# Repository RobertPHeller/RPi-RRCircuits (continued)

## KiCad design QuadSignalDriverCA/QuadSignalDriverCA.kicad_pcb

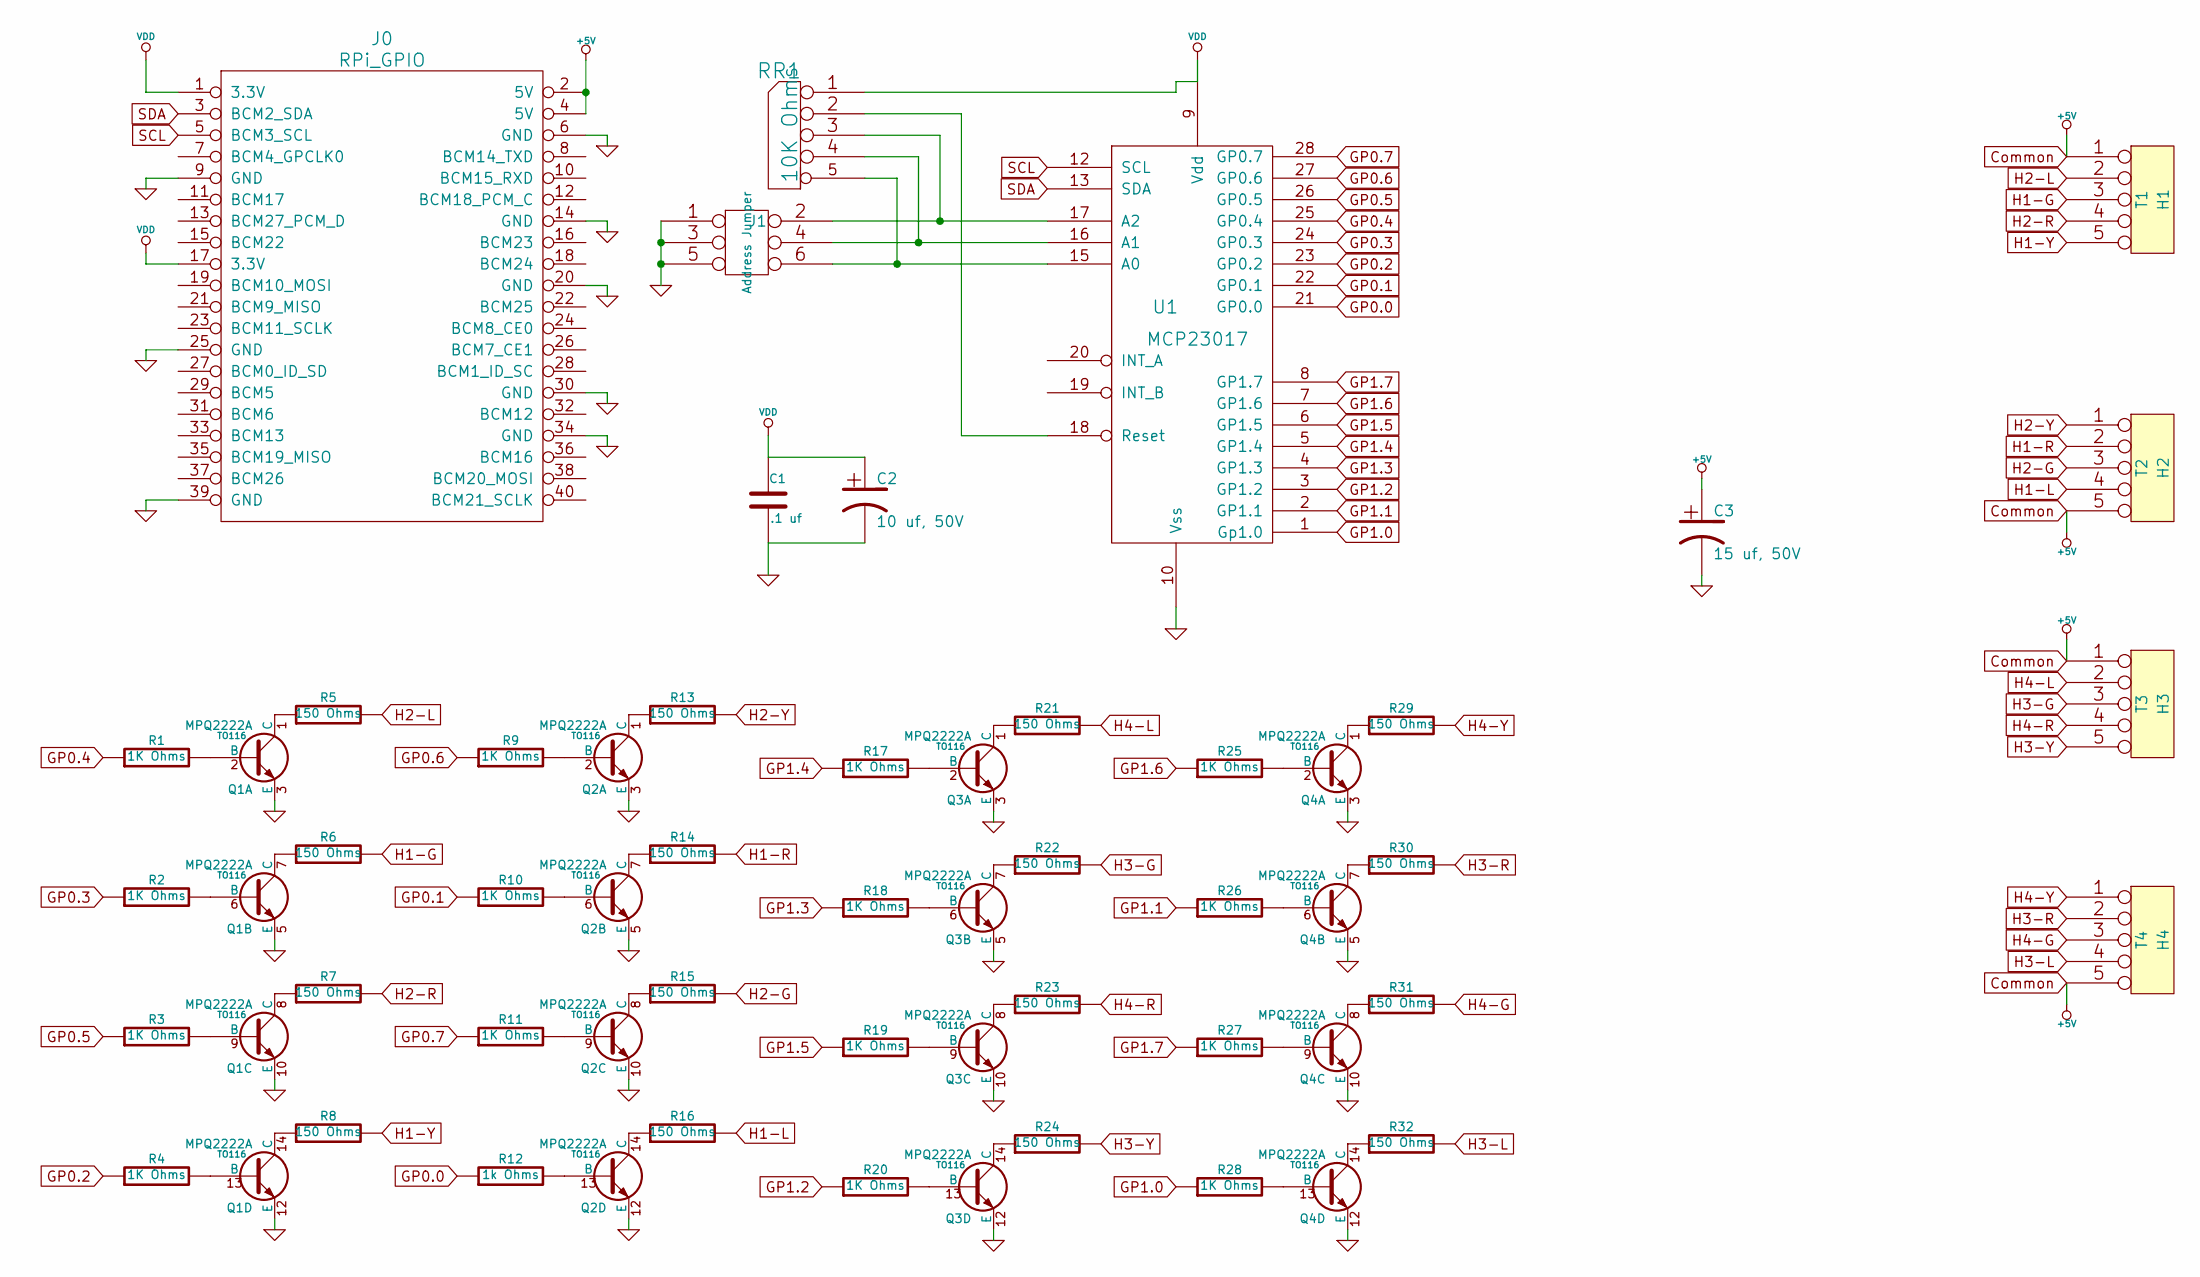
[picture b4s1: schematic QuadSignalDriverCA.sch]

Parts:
C1: .1 uf
C2: 10 uf, 50V
C3: 15 uf, 50V
J0: RPi_GPIO; Pin_Header_Straight_2x20
J1: Address Jumper
Q1, Q2, Q3, Q4: MPQ2222A; TO116
R1, R2, R3, R4, R9, R10, R11, R17, R18, R19, R20, R25, R26, R27, R28: 1K Ohms
R5, R6, R7, R8, R13, R14, R15, R16, R21, R22, R23, R24, R29, R30, R31, R32: 150 Ohms
R12: 1k Ohms
RR1: 10K Ohms
T1: H1
T2: H2
T3: H3
T4: H4
U1: MCP23017

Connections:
Common: C3.1, J0.2 (5V), J0.4 (5V), T1.1, T2.5, T3.1, T4.5
GND: C1.2, C2.2, C3.2, J0.6 (GND), J0.9 (GND), J0.14 (GND), J0.20 (GND), J0.25 (GND), J0.30 (GND), J0.34 (GND), J0.39 (GND), J1.1, J1.3, J1.5, Q1.3 (E), Q1.5 (E), Q1.10 (E), Q1.12 (E), Q2.3 (E), Q2.5 (E), Q2.10 (E), Q2.12 (E), Q3.3 (E), Q3.5 (E), Q3.10 (E), Q3.12 (E), Q4.3 (E), Q4.5 (E), Q4.10 (E), Q4.12 (E), U1.10 (Vss)
GP0.0: R12.1, U1.21 (GP0.0)
GP0.1: R10.1, U1.22 (GP0.1)
GP0.2: R4.1, U1.23 (GP0.2)
GP0.3: R2.1, U1.24 (GP0.3)
GP0.4: R1.1, U1.25 (GP0.4)
GP0.5: R3.1, U1.26 (GP0.5)
GP0.6: R9.1, U1.27 (GP0.6)
GP0.7: R11.1, U1.28 (GP0.7)
GP1.0: R28.1, U1.1 (Gp1.0)
GP1.1: R26.1, U1.2 (GP1.1)
GP1.2: R20.1, U1.3 (GP1.2)
GP1.3: R18.1, U1.4 (GP1.3)
GP1.4: R17.1, U1.5 (GP1.4)
GP1.5: R19.1, U1.6 (GP1.5)
GP1.6: R25.1, U1.7 (GP1.6)
GP1.7: R27.1, U1.8 (GP1.7)
H1-G: R6.2, T1.3
H1-L: R16.2, T2.4
H1-R: R14.2, T2.2
H1-Y: R8.2, T1.5
H2-G: R15.2, T2.3
H2-L: R5.2, T1.2
H2-R: R7.2, T1.4
H2-Y: R13.2, T2.1
H3-G: R22.2, T3.3
H3-L: R32.2, T4.4
H3-R: R30.2, T4.2
H3-Y: R24.2, T3.5
H4-G: R31.2, T4.3
H4-L: R21.2, T3.2
H4-R: R23.2, T3.4
H4-Y: R29.2, T4.1
unnamed: Q4.14 (C), R32.1
unnamed: Q4.13 (B), R28.2
unnamed: J1.6, RR1.5, U1.15 (A0)
unnamed: J1.4, RR1.4, U1.16 (A1)
unnamed: J1.2, RR1.3, U1.17 (A2)
unnamed: RR1.2, U1.18 (Reset)
unnamed: Q1.6 (B), R2.2
unnamed: Q1.7 (C), R6.1
unnamed: Q1.1 (C), R5.1
unnamed: Q1.2 (B), R1.2
unnamed: Q2.2 (B), R9.2
unnamed: Q2.1 (C), R13.1
unnamed: Q1.14 (C), R8.1
unnamed: Q1.13 (B), R4.2
unnamed: Q1.8 (C), R7.1
unnamed: Q1.9 (B), R3.2
unnamed: Q4.2 (B), R25.2
unnamed: Q4.1 (C), R29.1
unnamed: Q3.14 (C), R24.1
unnamed: Q3.13 (B), R20.2
unnamed: Q3.8 (C), R23.1
unnamed: Q3.9 (B), R19.2
unnamed: Q4.8 (C), R31.1
unnamed: Q4.9 (B), R27.2
unnamed: Q4.7 (C), R30.1
unnamed: Q4.6 (B), R26.2
unnamed: Q2.8 (C), R15.1
unnamed: Q2.9 (B), R11.2
unnamed: Q2.7 (C), R14.1
unnamed: Q2.6 (B), R10.2
unnamed: Q3.7 (C), R22.1
unnamed: Q3.6 (B), R18.2
unnamed: Q3.1 (C), R21.1
unnamed: Q3.2 (B), R17.2
unnamed: Q2.14 (C), R16.1
unnamed: Q2.13 (B), R12.2
SCL: J0.5 (BCM3_SCL), U1.12 (SCL)
SDA: J0.3 (BCM2_SDA), U1.13 (SDA)
VDD: C1.1, C2.1, J0.1 (3.3V), J0.17 (3.3V), RR1.1 (COM), U1.9 (Vdd)

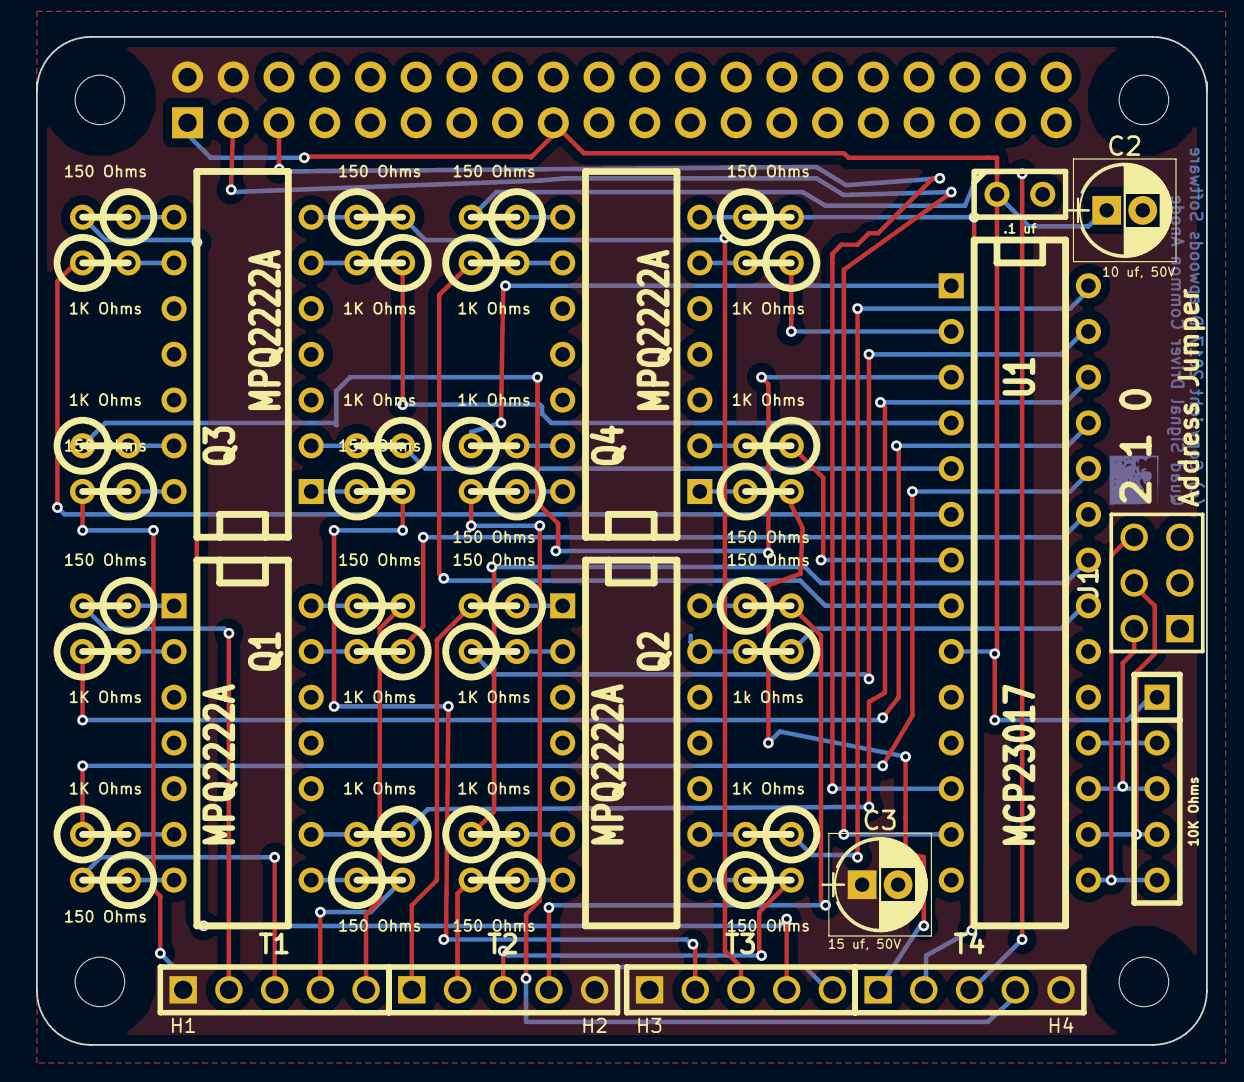
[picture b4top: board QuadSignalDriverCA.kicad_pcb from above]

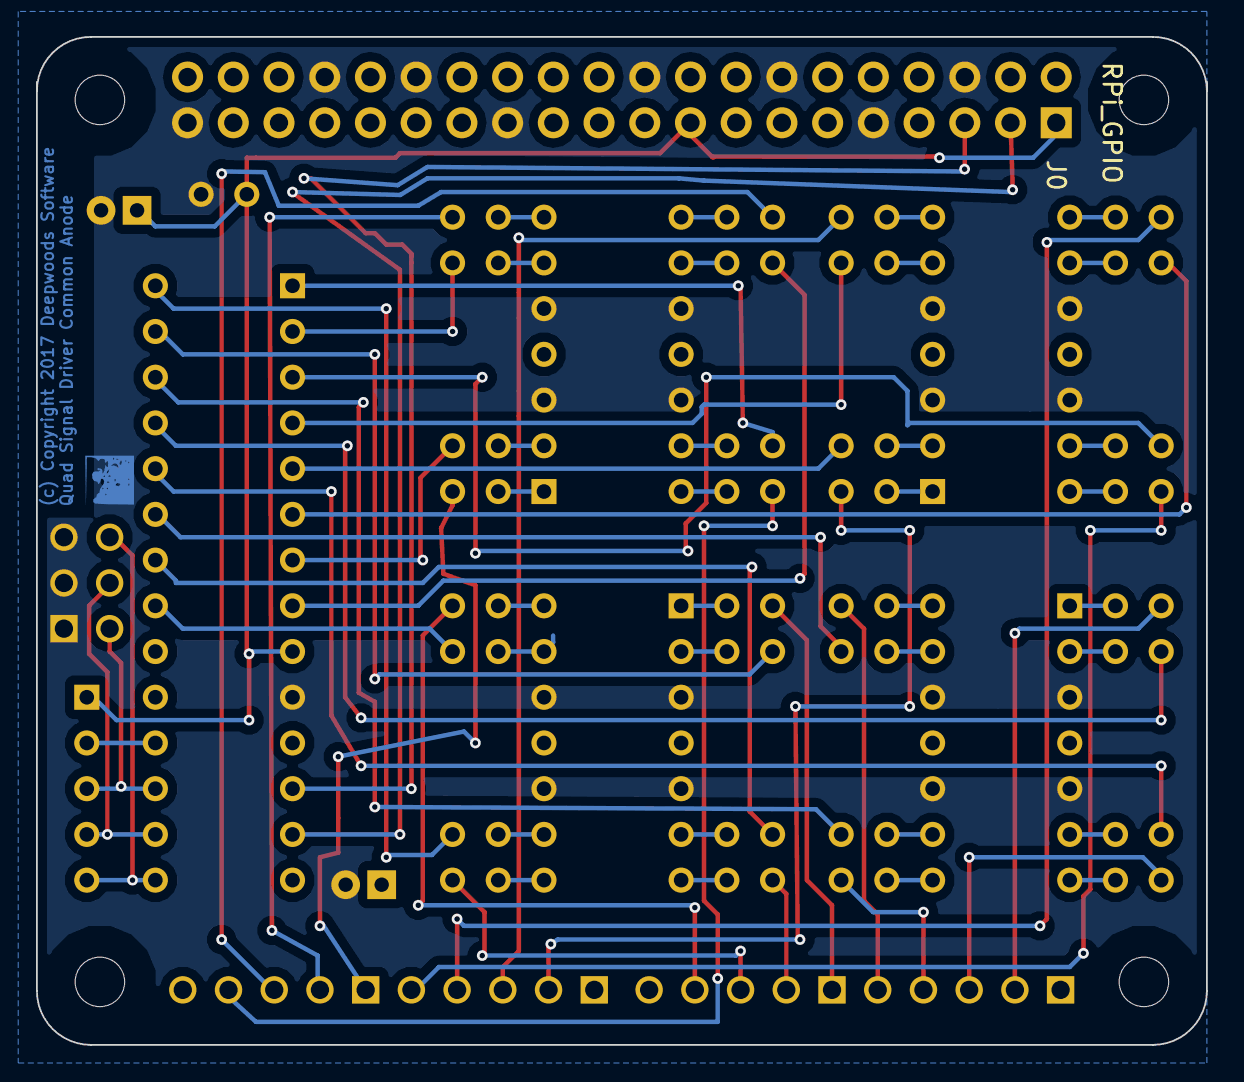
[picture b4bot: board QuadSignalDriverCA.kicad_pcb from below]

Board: 2 copper layers, 65.0 x 56.0 mm, 51 parts (5 on the bottom side), 73 nets.

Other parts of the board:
H1, H2, H3, H4: RPi_Hat_Mounting_Hole

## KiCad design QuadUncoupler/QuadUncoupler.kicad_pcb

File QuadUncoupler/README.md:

# QuadUncoupler

This is a generic qad version of DualUncouplerHAT.

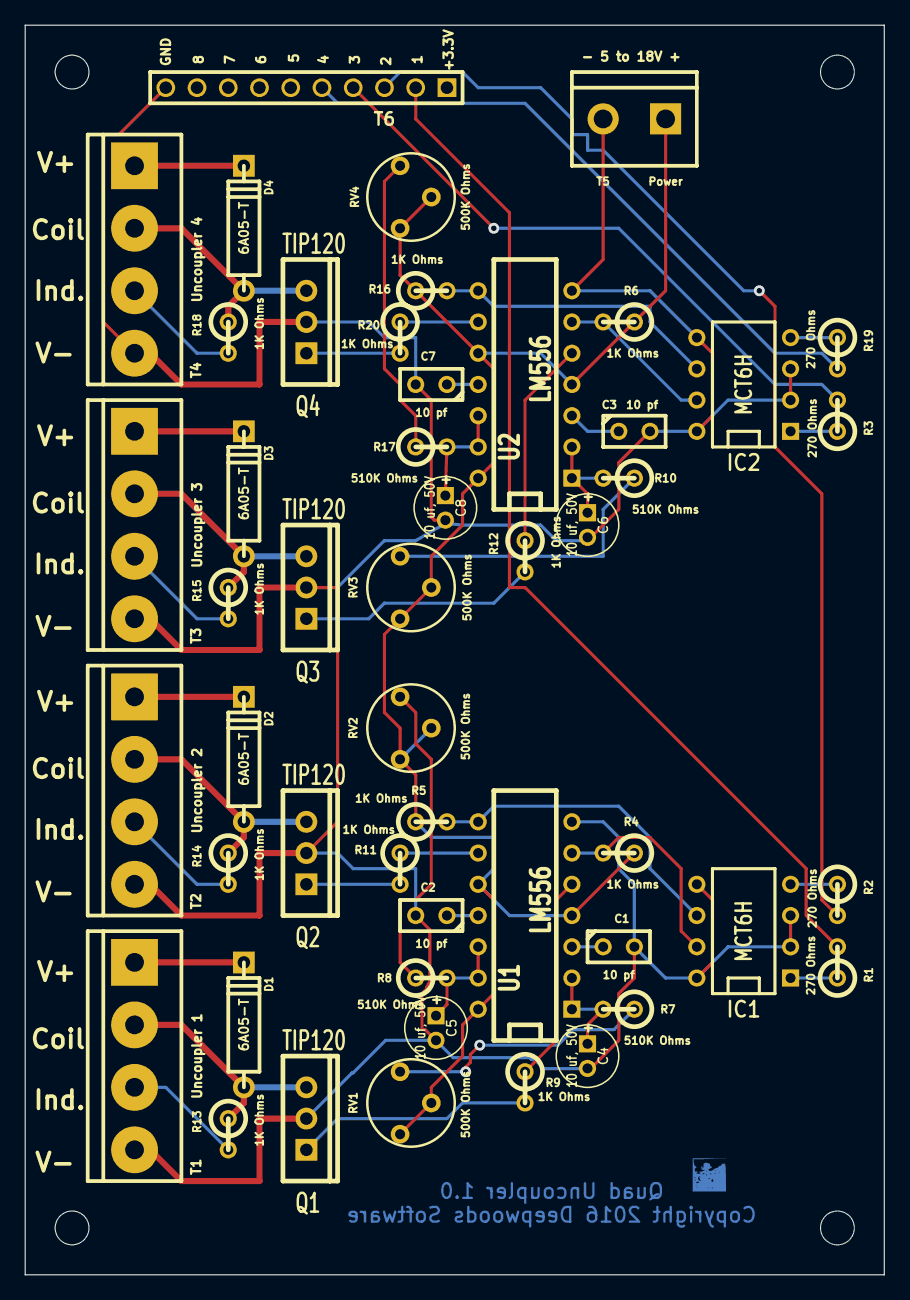
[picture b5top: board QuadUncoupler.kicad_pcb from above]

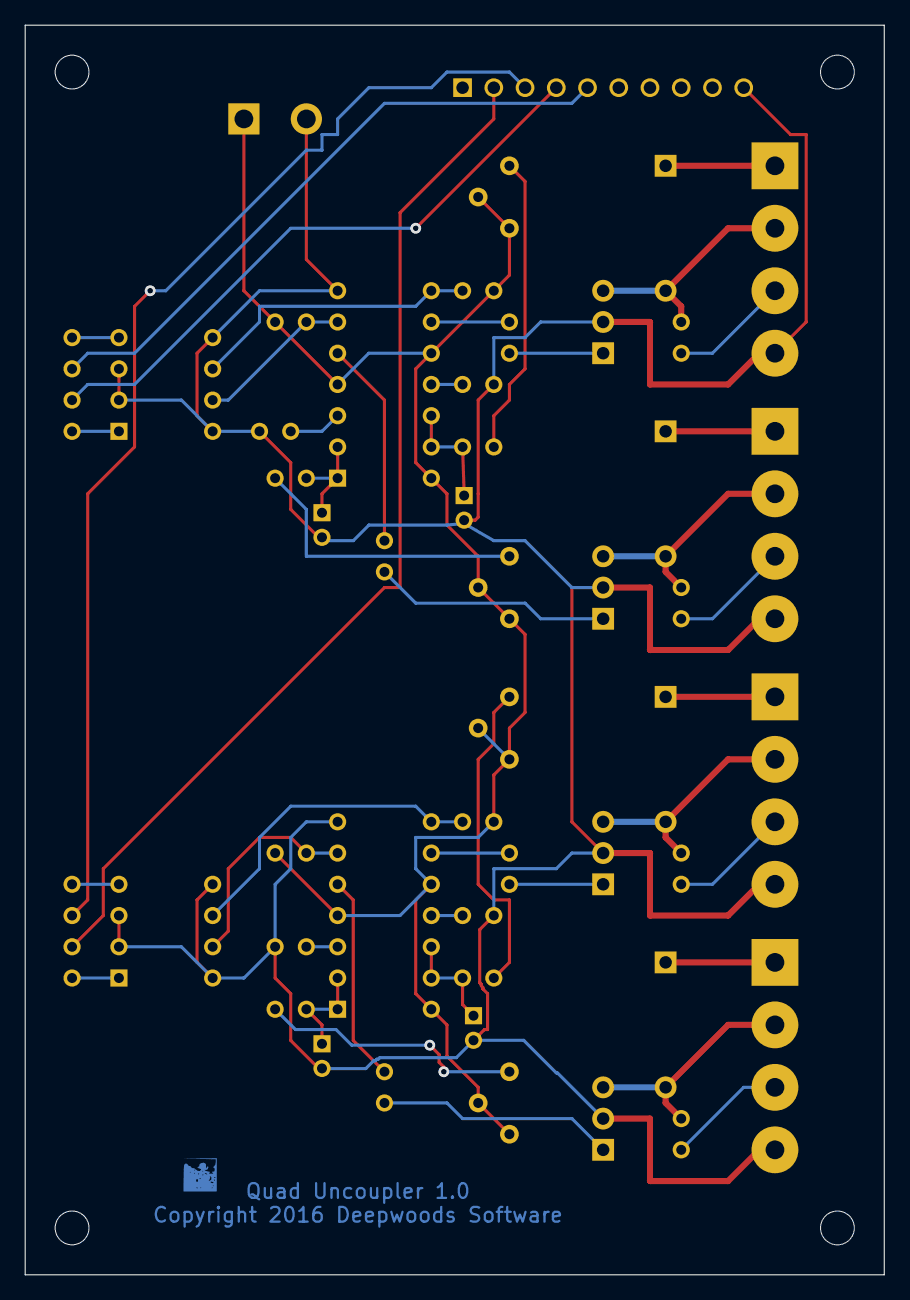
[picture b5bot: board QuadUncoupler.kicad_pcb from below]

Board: 2 copper layers, 69.8 x 101.6 mm, 54 parts (4 on the bottom side), 46 nets.

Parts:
C1, C2, C3, C7: 10 pf; C1
C4, C5, C6, C8: 10 uf, 50V; C1V5
D1, D2, D3, D4: 6A05-T; D4
H2, H2#2, H2#3, H2#4: RPi_Hat_Mounting_Hole
IC1, IC2: MCT6H; DIP-8__300
Q1, Q2, Q3, Q4: TIP120; TO220_VERT
R1, R2, R3, R19: 270 Ohms; R1
R4, R5, R6, R9, R11, R12, R13, R14, R15, R16, R18, R20: 1K Ohms; R1
R7, R8, R10, R17: 510K Ohms; R1
RV1, RV2, RV3, RV4: 500K Ohms; RV2
T1: Uncoupler 1; bornier4
T2: Uncoupler 2; bornier4
T3: Uncoupler 3; bornier4
T4: Uncoupler 4; bornier4
T5: Power; bornier2
T6: GPIO; ScrewTerm_2.54-10
U1, U2: LM556; DIP-14__300

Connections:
/Coil 1: D1.1, Q1.2, R13.1, T1.2
/Coil 2: D2.1, Q2.2, R14.1, T2.2
/Coil 3: D3.1, Q3.2, R15.1, T3.2
/Coil 4: D4.1, Q4.2, R18.1, T4.2
/Coupler 1 Power: D1.2, T1.1
/Coupler 2 Power: D2.2, T2.1
/Coupler 3 Power: D3.2, T3.1
/Coupler 4 Power: D4.2, T4.1
GND: C1.2, C2.2, C3.2, C4.2, C5.2, C6.2, C7.2, C8.2, IC1.2, IC1.3, IC1.5, IC1.8, IC2.2, IC2.3, IC2.5, IC2.8, Q1.3, Q2.3, Q3.3, Q4.3, T1.4, T2.4, T3.4, T4.4, T5.2, T6.10, U1.7, U2.7
GPIO.1: R1.2, T6.2
GPIO.2: R2.2, T6.3
GPIO.3: R3.2, T6.4
GPIO.4: R19.2, T6.5
unnamed: IC2.6, R16.2, U2.8
unnamed: IC2.4, R19.1
unnamed: R13.2, T1.3
unnamed: C8.1, R17.2, U2.12, U2.13
unnamed: C7.1, U2.11
unnamed: R7.1, RV1.1
unnamed: C4.1, R7.2, U1.1, U1.2
unnamed: C1.1, U1.3
unnamed: Q1.1, R9.2
unnamed: R9.1, U1.5
unnamed: Q4.1, R20.2
unnamed: R20.1, U2.9
unnamed: R17.1, RV4.1
unnamed: R18.2, T4.3
unnamed: Q3.1, R12.2
unnamed: R12.1, U2.5
unnamed: R10.1, RV3.1
unnamed: IC1.6, R5.2, U1.8
unnamed: IC1.4, R2.1
unnamed: R15.2, T3.3
unnamed: IC2.7, R6.2, U2.6
unnamed: C6.1, R10.2, U2.1, U2.2
unnamed: IC2.1, R3.1
unnamed: C3.1, U2.3
unnamed: IC1.1, R1.1
unnamed: R14.2, T2.3
unnamed: IC1.7, R4.2, U1.6
unnamed: C2.1, U1.11
unnamed: Q2.1, R11.2
unnamed: R11.1, U1.9
unnamed: C5.1, R8.2, U1.12, U1.13
unnamed: R8.1, RV2.1
VCC: R4.1, R5.1, R6.1, R16.1, RV1.2, RV1.3, RV2.2, RV2.3, RV3.2, RV3.3, RV4.2, RV4.3, T5.1, U1.4, U1.10, U1.14, U2.4, U2.10, U2.14

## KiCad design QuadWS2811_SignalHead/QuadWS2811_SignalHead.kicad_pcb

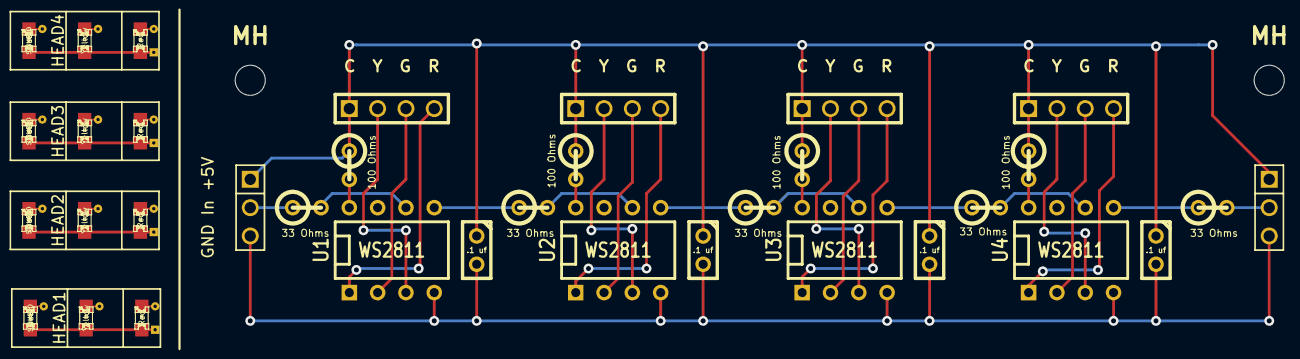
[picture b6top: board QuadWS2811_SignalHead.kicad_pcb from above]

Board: 2 copper layers, 29 parts (0 on the bottom side), 28 nets.

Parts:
C1, C2, C3, C4: .1 uf; C1
HEAD1, HEAD2, HEAD3, HEAD4: SIGHEAD; SH3
K1: GND In +5V; PIN_ARRAY_3X1
K2: GND Out +5V; PIN_ARRAY_3X1
MH: MountingHole_2-7mm_RevA_Date21Jun2010
MH#2: MountingHole_2-7mm_RevA_Date21Jun2010
P1, P2, P3, P4: C Y G R; ScrewTerm_2.54-4
R1, R3, R5, R7, R9: 33 Ohms; R1
R2, R4, R6, R8: 100 Ohms; R1
U1, U2, U3, U4: WS2811; DIP-8__300

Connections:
+5V: C1.1, C2.1, C3.1, C4.1, K1.1, K2.1, P1.1, P2.1, P3.1, P4.1, R2.1, R4.1, R6.1, R8.1
GND: C1.2, C2.2, C3.2, C4.2, K1.3, K2.3, U1.4, U2.4, U3.4, U4.4
unnamed: K1.2, R1.1
unnamed: R1.2, U1.6
unnamed: R3.1, U1.5
unnamed: R3.2, U2.6
unnamed: R5.1, U2.5
unnamed: R5.2, U3.6
unnamed: R7.1, U3.5
unnamed: R7.2, U4.6
unnamed: R9.1, U4.5
unnamed: K2.2, R9.2
unnamed: R6.2, U3.8
unnamed: P3.2, U3.3
unnamed: P3.3, U3.2
unnamed: P3.4, U3.1
unnamed: P4.2, U4.3
unnamed: R8.2, U4.8
unnamed: P4.3, U4.2
unnamed: P4.4, U4.1
unnamed: R2.2, U1.8
unnamed: P1.2, U1.3
unnamed: P1.3, U1.2
unnamed: P1.4, U1.1
unnamed: R4.2, U2.8
unnamed: P2.2, U2.3
unnamed: P2.3, U2.2
unnamed: P2.4, U2.1
